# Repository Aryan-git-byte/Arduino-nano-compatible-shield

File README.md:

# Arduino Nano Compatible Shield

## overview:

This project is a custom Arduino Nano compatible robotics shield designed to simplify building a 2WD robot car with integrations of many sensors such as ir sensor, ultrasonic, mpu6050 and communication device as bluetooth       
The ultimate goal is to eliminate all those messy wirings , and solderings that we do while making simple 2wd cars packed with features in affordable range.    

## Features:
- U can drive 2 motors with this shield 
- u can integrate 3 ir sensors, 1 ultrasonic sensor, 1 mpu6050, 1 HC-05, and 2 servos

## How to use:
1. insert arduino nano
2. flash the nano with the firmware(change acocrding to your need)
3. connect all the sensors, motors, u need.
4. power the board and operate it

## firmware: Basic firmware written in .ino

## PCB :
### Schematic:

### PCB:        
top layer:
       
bottom layer:       
     
F.silkscreen:       
    
B.silkscreen:

3d:

# Cost Breakdown:

# For the Shield
|item name| quantity | description | link |cost|
|---------|----------|-------------|------|----|
|PCB manufacturing(5)|1 |production/gerber.zip|from robu|950 rs (10.33 usd)
|male header x 40|1|for connectors | https://quartzcomponents.com/products/40-pin-break-away-headers-straight-male-headers| 7 rs|
female hedaersx40|2|for arduino nano & conectors| https://quartzcomponents.com/products/40-pin-straight-female-berg-strips| 10 rs|
l293d|1 | motor driver ic | https://quartzcomponents.com/products/l293d-motor-driver-ic| 19 rs|
buzzer|1|buzzzz|https://quartzcomponents.com/products/piezo-buzzer|13 rs|
2 pin screw terminal|3| for motor outputs and power inputs| https://quartzcomponents.com/products/2-pin-pcb-mount-terminal-block-screw-type?variant=37646366474424&country=IN&currency=INR&utm_medium=product_sync&utm_source=google&utm_content=sag_organic&utm_campaign=sag_organic?utm_source=google&utm_medium=FreeListings| rs 4|
l7805|1|voltage regulator| https://quartzcomponents.com/products/lm7805-5v-positive-regulator?variant=31898041942151&country=IN&currency=INR&utm_medium=product_sync&utm_source=google&utm_content=sag_organic&utm_campaign=sag_organic?utm_source=google&utm_medium=FreeListings| rs 8 
mini heatsink for l7805| 1| to absorb the heat of the l7805| https://quartzcomponents.com/products/22-15-10mm-black-aluminum-heat-sink-for-to-220-package-power-transistor-cooling?variant=45643070800106&country=IN&currency=INR&utm_medium=product_sync&utm_source=google&utm_content=sag_organic&utm_campaign=sag_organic?utm_source=google&utm_medium=FreeListings| rs 19|
led|1|for the status| https://quartzcomponents.com/products/red-5mm-led| rs 2
100 nf ceramic| 6| for decoupling | https://quartzcomponents.com/products/10000-pf-0-1uf-ceramic-capacitor?variant=31898110197895&country=IN&currency=INR&utm_medium=product_sync&utm_source=google&utm_content=sag_organic&utm_campaign=sag_organic?utm_source=google&utm_medium=FreeListings| rs 5
470 uF electrolytic| 2| for safety| https://quartzcomponents.com/products/470-%C2%B5f-25v-radial-electrolytic-capacitor-through-hole?variant=45660873916650&country=IN&currency=INR&utm_medium=product_sync&utm_source=google&utm_content=sag_organic&utm_campaign=sag_organic?utm_source=google&utm_medium=FreeListings| rs 5

# Assembly overview:
1. get all the parts listed in the BOMs including the chasis, pcb, modules etc.
2. solder them
3. now, start assembling the chasis using this guide:   

4. now, stick a servo on the front side above the castor wheel and put the ultrasonic mounting bracket on top of it and screw them.
5. now flash the code in `firmware/main.ino`
6. enjoy
## cart: 

## Total(incl. of shipping, gst etc):
### rs 223(2.54 usd) + 950 rs(10.33 usd) = 1173 rs(12.77 usd)
.        
.
# For the 2wd car:

|Item name | quantity| link | price|
|----------|---------|------|------|
|2wd chasis car set|1|https://robocraze.com/products/2wd-two-wheel-drive-diy-kit-a-smart-robot-car-with-chassis?variant=40192705036441&country=IN&currency=INR&utm_medium=product_sync&utm_source=google&utm_content=sag_organic&utm_campaign=sag_organic|rs 289
|servo|1|https://robocraze.com/products/sg90-micro-servo-motor?variant=40192525238425| rs 109
|ir sensor| 3 | https://robocraze.com/products/ir-proximity-sensor-1?variant=40192623640729&country=IN&currency=INR&utm_medium=product_sync&utm_source=google&utm_content=sag_organic&utm_campaign=sag_organic| rs 29
|HC-05|1|https://robocraze.com/products/hc-05-bluetooth-module?variant=40193264189593&country=IN&currency=INR&utm_medium=product_sync&utm_source=google&utm_content=sag_organic&utm_campaign=sag_organic|rs 224
|HC-SR04|1|https://robocraze.com/products/hc-sr-04-ultrasonic-sensor?variant=40192340983961&country=IN&currency=INR&utm_medium=product_sync&utm_source=google&utm_content=sag_organic&utm_campaign=sag_organic|rs 74|
|hc-sr04 mounting bracket| 1 | https://robocraze.com/products/mounting-bracket-for-hc-sr04-ultrasonic-module?variant=43394849112288&country=IN&currency=INR&utm_medium=product_sync&utm_source=google&utm_content=sag_organic&utm_campaign=sag_organic| rs 20|
|mpu6050|1|https://robocraze.com/products/mpu-6050-triple-axis-accelerometer-gyroscope-module?variant=40192322011289&country=IN&currency=INR&utm_medium=product_sync&utm_source=google&utm_content=sag_organic&utm_campaign=sag_organic|rs 175|

## cart:

## Total = 852 rs for the 2wd car components

# Total(inclduing the pcb, components and shield):
## PCB - 950 rs
## Shield - 223 rs
## component = 852 rs
## Total = 2025 rs(22.01 usd)

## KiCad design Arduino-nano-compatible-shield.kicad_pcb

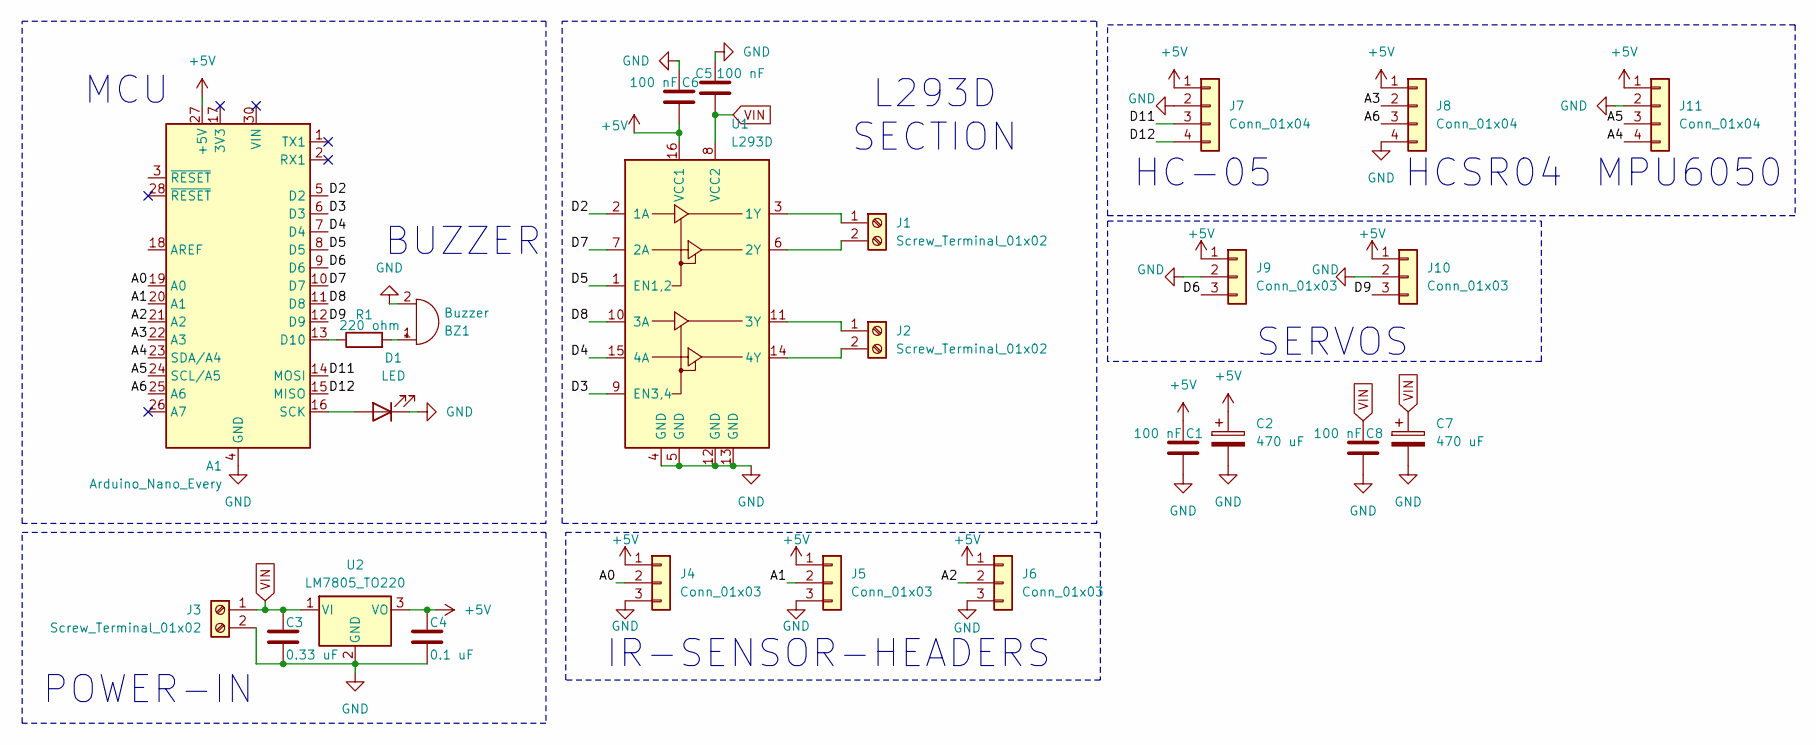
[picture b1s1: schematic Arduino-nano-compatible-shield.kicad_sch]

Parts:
A1: Arduino_Nano_Every; Arduino_Nano
BZ1: Buzzer; Buzzer_12x9.5RM7.6
C1, C5, C6, C8: 100 nF; C_Disc_D5.0mm_W2.5mm_P2.50mm
C2, C7: 470 uF; CP_Radial_D8.0mm_P3.50mm
C3: 0.33 uF; C_Disc_D5.0mm_W2.5mm_P2.50mm
C4: 0.1 uF; C_Disc_D5.0mm_W2.5mm_P2.50mm
D1: LED; LED_D5.0mm
J1, J2, J3: Screw_Terminal_01x02; TE_282837-2
J4, J5, J6, J9, J10: Conn_01x03; PinHeader_1x03_P2.54mm_Vertical
J7, J8, J11: Conn_01x04; PinHeader_1x04_P2.54mm_Vertical
R1: 220 ohm; R_Axial_DIN0207_L6.3mm_D2.5mm_P2.54mm_Vertical
U1: L293D; DIP-16_W7.62mm
U2: LM7805_TO220; TO-220-3_Vertical

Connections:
+5V: A1.27 (+5V), C1.1, C2.1, C4.1, C6.2, J4.1, J5.1, J6.1, J7.1, J8.1, J9.1, J10.1, J11.1, U1.16 (VCC1), U2.3 (VO)
/A0: A1.19 (A0), J4.2
/A1: A1.20 (A1), J5.2
/A2: A1.21 (A2), J6.2
/A3: A1.22 (A3), J8.2
/A4: A1.23 (SDA/A4), J11.4
/A5: A1.24 (SCL/A5), J11.3
/A6: A1.25 (A6), J8.3
/D2: A1.5 (D2), U1.2 (1A)
/D3: A1.6 (D3), U1.9 (EN3,4)
/D4: A1.7 (D4), U1.15 (4A)
/D5: A1.8 (D5), U1.1 (EN1,2)
/D6: A1.9 (D6), J9.3
/D7: A1.10 (D7), U1.7 (2A)
/D8: A1.11 (D8), U1.10 (3A)
/D9: A1.12 (D9), J10.3
/D11: A1.14 (MOSI), J7.3
/D12: A1.15 (MISO), J7.4
GND: A1.4 (GND), A1.29 (GND), BZ1.2 (-), C1.2, C2.2, C3.2, C4.2, C5.1, C6.1, C7.2, C8.2, D1.1 (K), J3.2, J4.3, J5.3, J6.3, J7.2, J8.4, J9.2, J10.2, J11.2, U1.4 (GND), U1.5 (GND), U1.12 (GND), U1.13 (GND), U2.2 (GND)
unnamed: A1.13 (D10), R1.1
unnamed: A1.16 (SCK), D1.2 (A)
unnamed: BZ1.1 (+), R1.2
unnamed: J1.1, U1.3 (1Y)
unnamed: J1.2, U1.6 (2Y)
unnamed: J2.1, U1.11 (3Y)
unnamed: J2.2, U1.14 (4Y)
VIN: C3.1, C5.2, C7.1, C8.1, J3.1, U1.8 (VCC2), U2.1 (VI)

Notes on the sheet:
L293D SECTION
MPU6050
MCU
HC-05
HCSR04
SERVOS
POWER-IN
IR-SENSOR-HEADERS
BUZZER

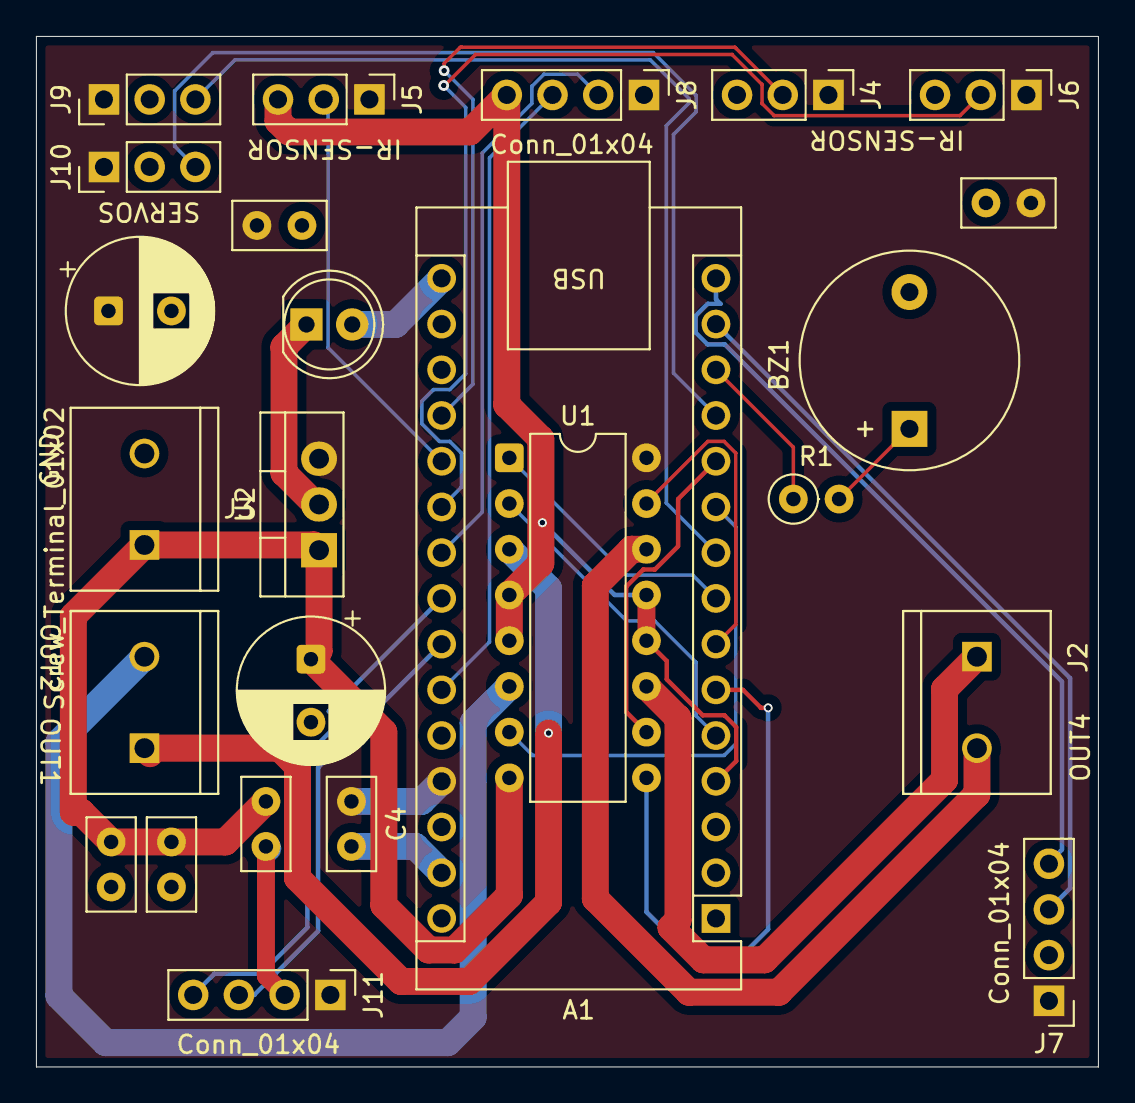
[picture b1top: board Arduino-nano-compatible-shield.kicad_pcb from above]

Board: 2 copper layers, 59.0 x 57.2 mm, 25 parts (0 on the bottom side), 27 nets.

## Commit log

2026-02-19 git init
2026-03-14 update bom
2026-05-15 complete
